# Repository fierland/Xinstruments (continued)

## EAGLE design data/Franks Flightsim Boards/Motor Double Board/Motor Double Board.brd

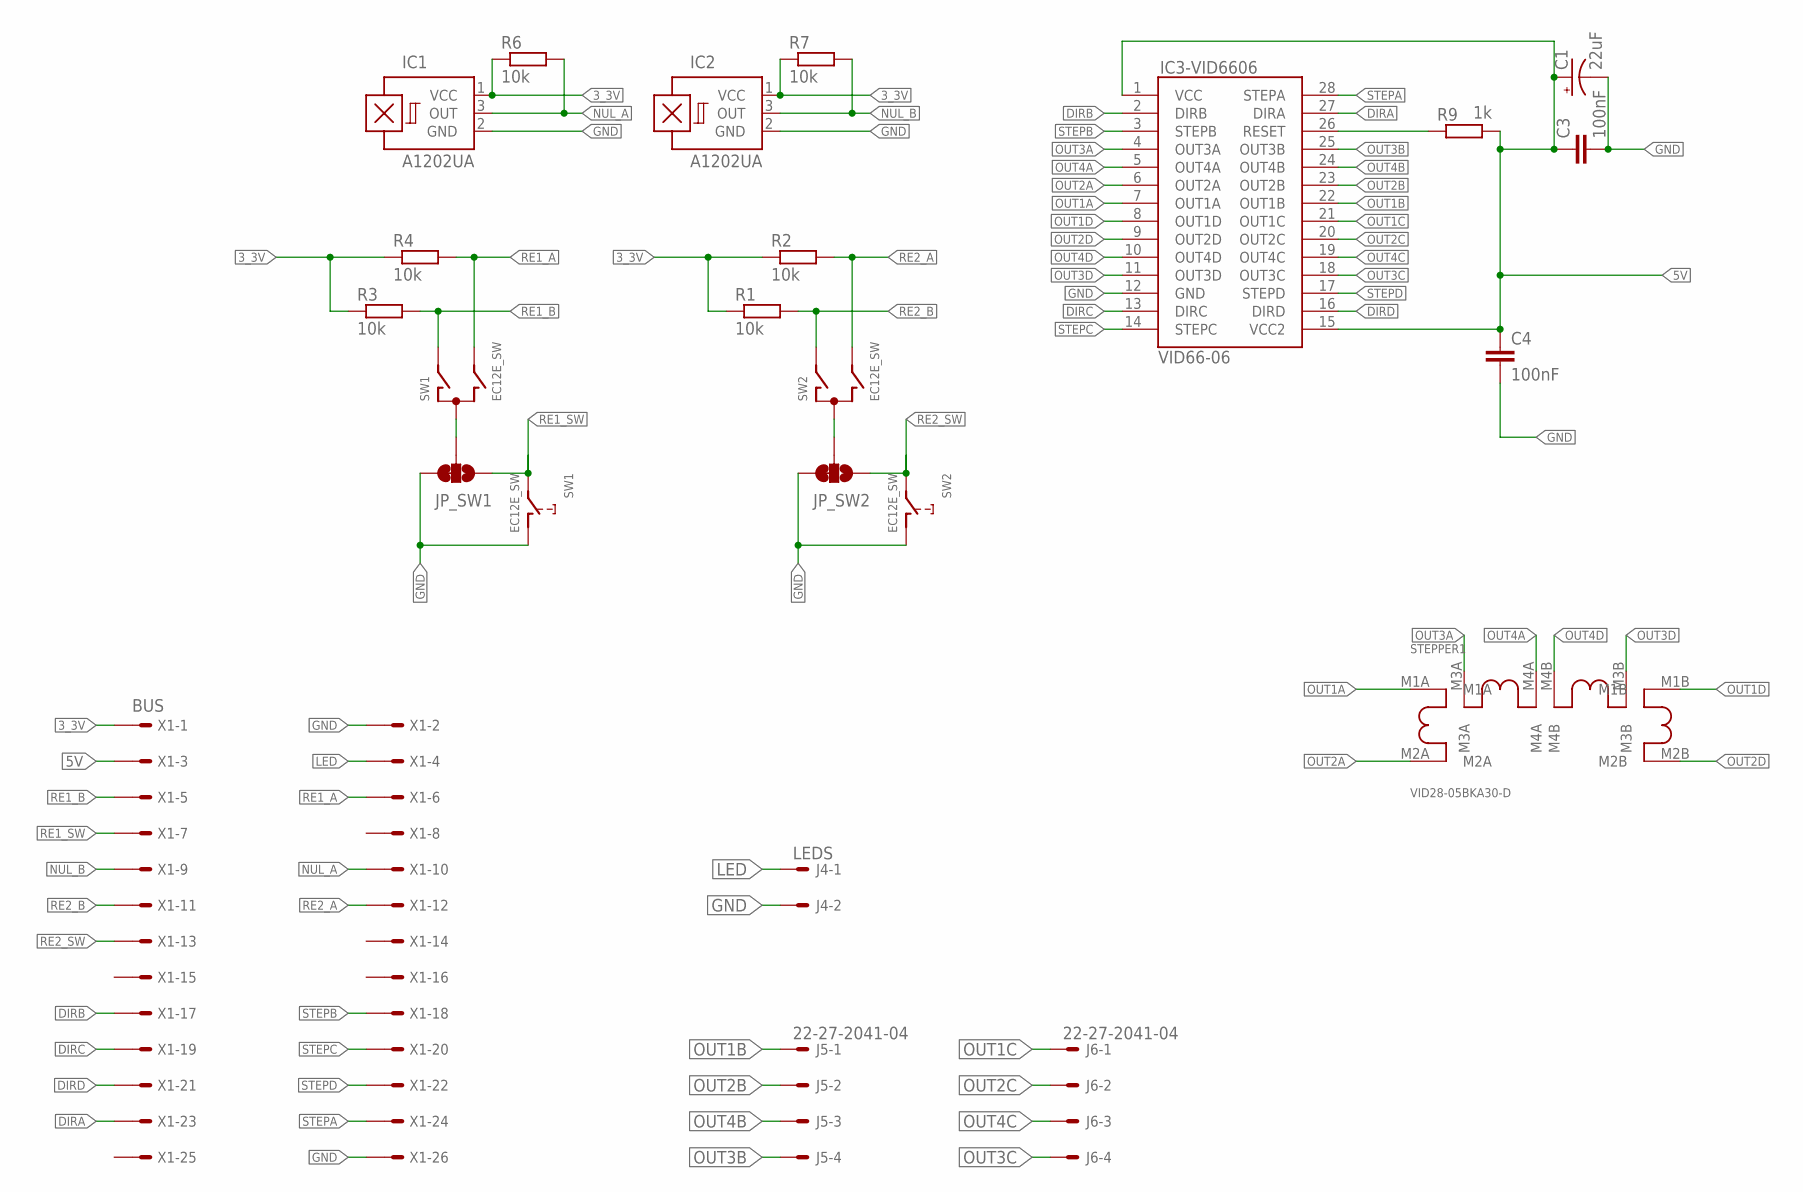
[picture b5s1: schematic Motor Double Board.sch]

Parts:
C1: 22uF; PANASONIC_C
C3, C4: 100nF; C0805
IC1, IC2: A1202UA; SIP3-UA
IC3-VID6606: VID66-06; SO28W
J4: LEDS; 6410-02
J5, J6: 22-27-2041-04; 6410-04
JP_SW1, JP_SW2: JUMPER-SMT_3_1-NC_TRACE_SILK; SMT-JUMPER_3_1-NC_TRACE_SILK
R1, R2, R3, R4, R6, R7: 10k; M1206
R9: 1k; M1206
STEPPER1: VID28-05BKA30-D; BKA30D-R5-BACK-DUAL
SW1, SW2: EC12E_SW; ALPS_EC12E_SW
X1: BUS; 057-026-1

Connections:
3_3V: IC1.1 (VCC), IC2.1 (VCC), R1.1, R2.1, R3.1, R4.1, R6.1, R7.1, X1.1
5V: C1.+, C3.1, C4.1, IC3-VID6606.1 (VCC), IC3-VID6606.15 (VCC2), R9.2, X1.3
DIRA: IC3-VID6606.27 (DIRA), X1.23
DIRB: IC3-VID6606.2 (DIRB), X1.17
DIRC: IC3-VID6606.13 (DIRC), X1.19
DIRD: IC3-VID6606.16 (DIRD), X1.21
GND: C1.-, C3.2, C4.2, IC1.2 (GND), IC2.2 (GND), IC3-VID6606.12 (GND), J4.2, JP_SW1.3, JP_SW2.3, SW1.D (1), SW2.D (1), X1.2, X1.26
LED: J4.1, X1.4
unnamed: JP_SW2.2, SW2.C
unnamed: JP_SW1.2, SW1.C
unnamed: IC3-VID6606.26 (RESET), R9.1
NUL_A: IC1.3 (OUT), R6.2, X1.10
NUL_B: IC2.3 (OUT), R7.2, X1.9
OUT1A: IC3-VID6606.7 (OUT1A), STEPPER1.M1A
OUT1B: IC3-VID6606.22 (OUT1B), J5.1
OUT1C: IC3-VID6606.21 (OUT1C), J6.1
OUT1D: IC3-VID6606.8 (OUT1D), STEPPER1.M1B
OUT2A: IC3-VID6606.6 (OUT2A), STEPPER1.M2A
OUT2B: IC3-VID6606.23 (OUT2B), J5.2
OUT2C: IC3-VID6606.20 (OUT2C), J6.2
OUT2D: IC3-VID6606.9 (OUT2D), STEPPER1.M2B
OUT3A: IC3-VID6606.4 (OUT3A), STEPPER1.M3A
OUT3B: IC3-VID6606.25 (OUT3B), J5.4
OUT3C: IC3-VID6606.18 (OUT3C), J6.4
OUT3D: IC3-VID6606.11 (OUT3D), STEPPER1.M3B
OUT4A: IC3-VID6606.5 (OUT4A), STEPPER1.M4A
OUT4B: IC3-VID6606.24 (OUT4B), J5.3
OUT4C: IC3-VID6606.19 (OUT4C), J6.3
OUT4D: IC3-VID6606.10 (OUT4D), STEPPER1.M4B
RE1_A: R4.2, SW1.B, X1.6
RE1_B: R3.2, SW1.A, X1.5
RE1_SW: JP_SW1.1, SW1.E (2), X1.7
RE2_A: R2.2, SW2.B, X1.12
RE2_B: R1.2, SW2.A, X1.11
RE2_SW: JP_SW2.1, SW2.E (2), X1.13
STEPA: IC3-VID6606.28 (STEPA), X1.24
STEPB: IC3-VID6606.3 (STEPB), X1.18
STEPC: IC3-VID6606.14 (STEPC), X1.20
STEPD: IC3-VID6606.17 (STEPD), X1.22

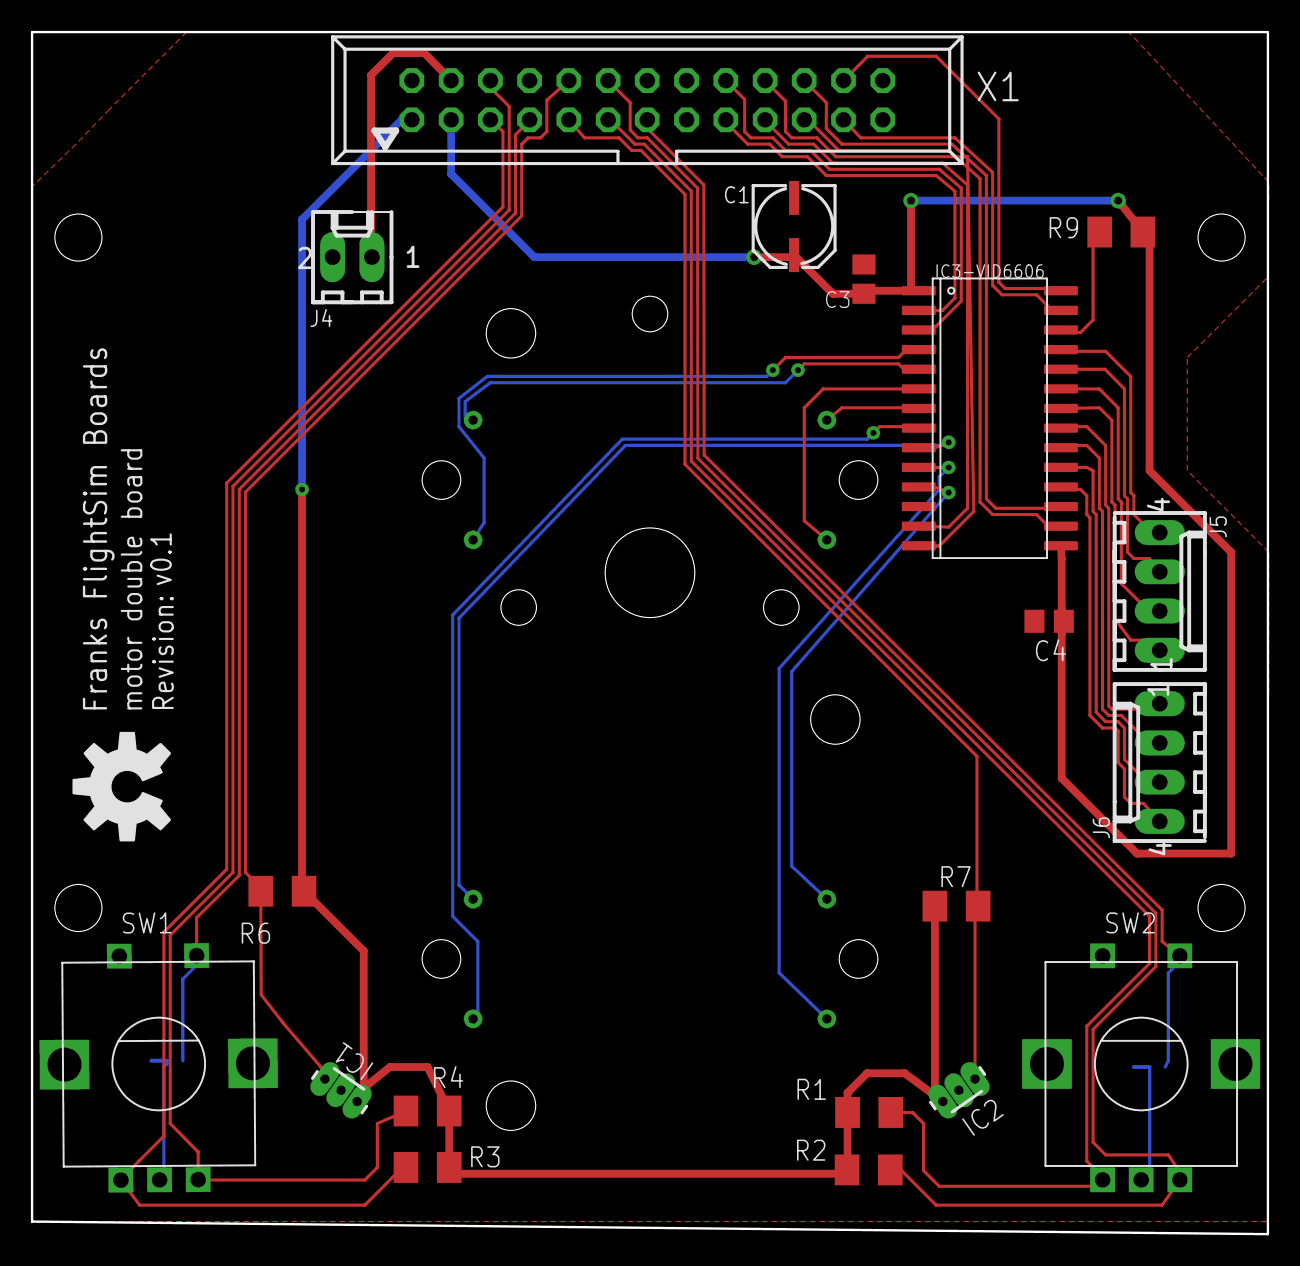
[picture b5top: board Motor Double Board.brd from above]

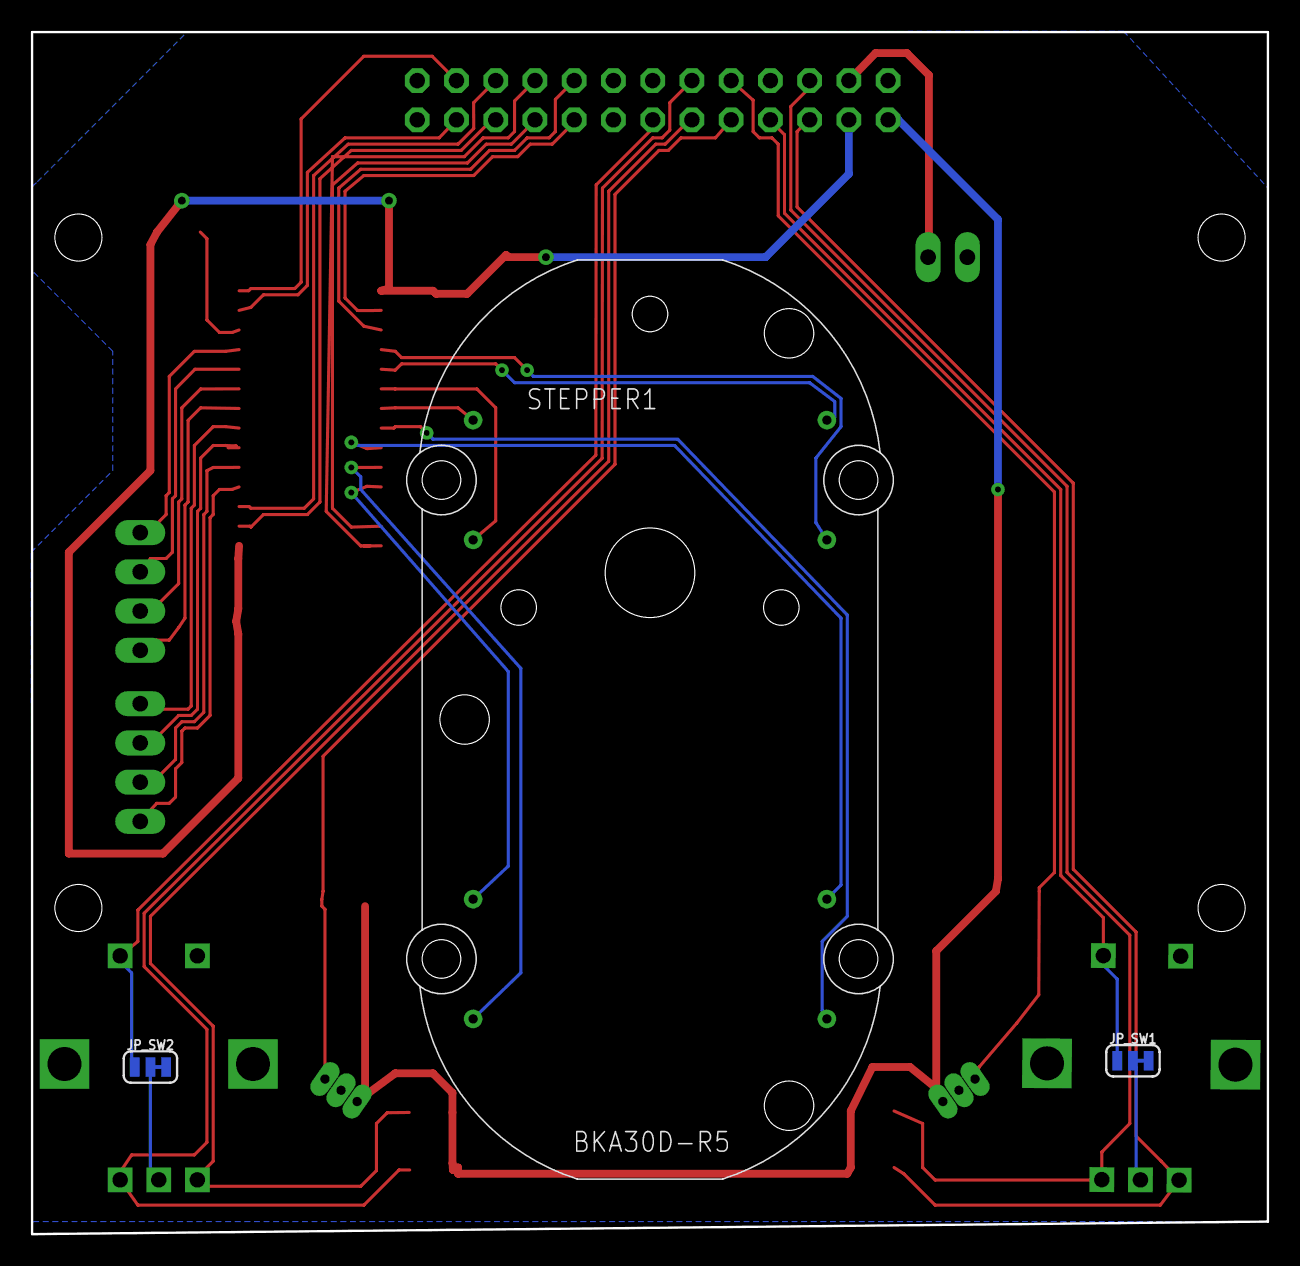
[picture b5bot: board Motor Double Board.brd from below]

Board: 2 copper layers, 80.0 x 77.8 mm, 27 parts (3 on the bottom side), 39 nets.

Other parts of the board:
U$1, U$11, U$12, U$13: STAND-OFF-TIGHT
U$9: OSHW-LOGO-L

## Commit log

2018-03-29 Initial code added
2018-03-29 adding the rest of the lib files in one repo
2018-03-30 restructure files
2018-03-30 restructure files and libs
2018-03-30 add eagle files
2018-03-30 work commit
2018-03-30 upload eagle files
2018-03-30 adding sketchup files
2018-03-30 daily commit still developing
2018-04-30 new PCB
    Updated with new pcb for 2_25 version
2018-04-30 git ignore adapted for eagle
    Gitignore adjusted
2018-04-30 error in pcb and new gitignore
2018-04-30 add Inventor files
2018-09-04 Update dev status
2018-09-13 update and backup
    Update
2018-09-17 backup
2018-09-18 sync
2018-09-25 save
2018-10-04 daily sync
2018-10-05 Daily Save
2018-10-09 daily
2018-10-18 commit new work
2018-10-19 dayly
2018-10-29 update working steppers
2018-11-12 reorganise for shared libraries
2019-01-11 added led blink
